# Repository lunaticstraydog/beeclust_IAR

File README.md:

# Implementation of an adated beeclust algorithm for mona robot
## Implementation details
3 versions :
version 1 is less sensitive (robots will not detect each others at great distances) and will work with a robot acting as the source (with light_emitter)
Version 2 is more sensitive and aggregates quicker generally.
It also is confirmed to work with a standard lamp acting as an IR source.
A few things to note :
- It is technically possible for a robot to wrongfully detect another robot as the source in the second algorithm, thought it did not happen in our testing
- The robot is supposed to wait longer (led are red in that case) the more robots it detected. (in the second algorithm).
	However, right now it only takes into account the robots it first detected, which is suboptimal and makes that feature work fairly badly (most often it will just consider one robot around it regardless)
- Blue state means the robot thinks it saw a source (in the second algo).
	In the subsequent 5 seconds ~ it will monitor its sensors to check whether it really was a source.
	It happens that it will mistake a robot for a source, will turn blue but will later change its mind. This is normal behavior.

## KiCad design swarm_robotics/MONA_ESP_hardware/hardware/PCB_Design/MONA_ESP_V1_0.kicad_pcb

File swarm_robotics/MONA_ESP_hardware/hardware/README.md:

# MONA ESP Hardware

## Schematic
The schematic for the board is given in a PDF file. The value of passive components is shown and the component code of the IC. 

## PCB design file
The PCB board file is given in [KiCad](www.kicad.org) format. It is neccesarry to use KiCad to open the board file.

## MONA ESP board design

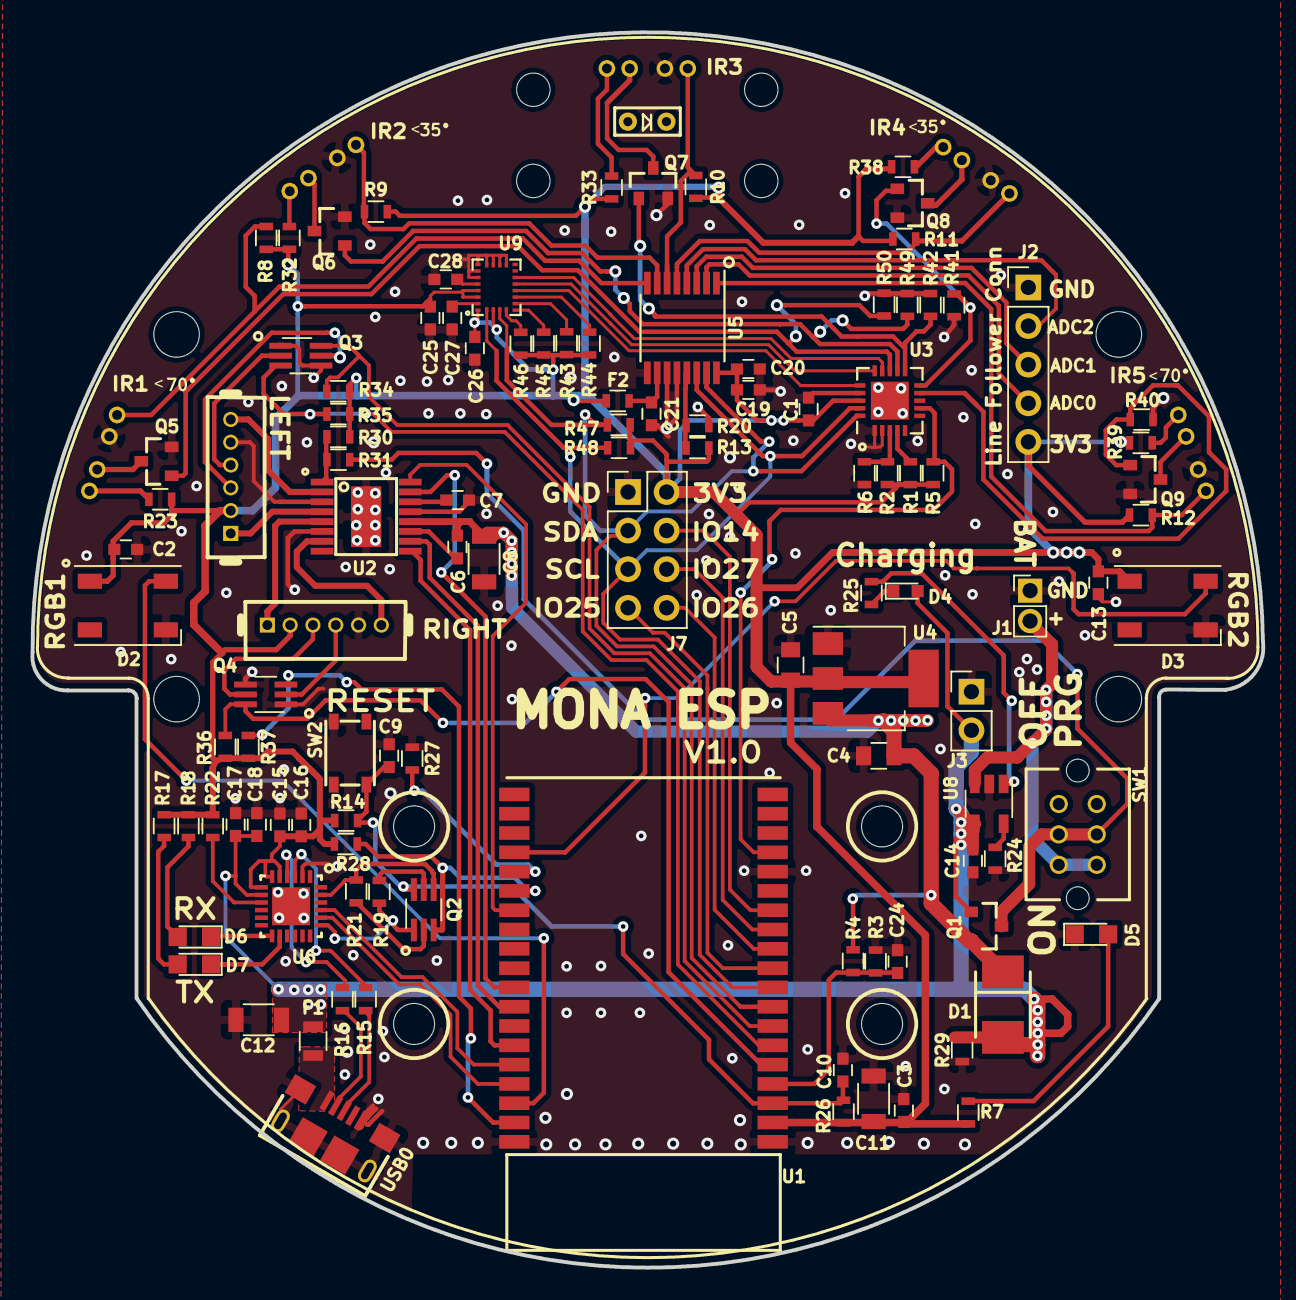
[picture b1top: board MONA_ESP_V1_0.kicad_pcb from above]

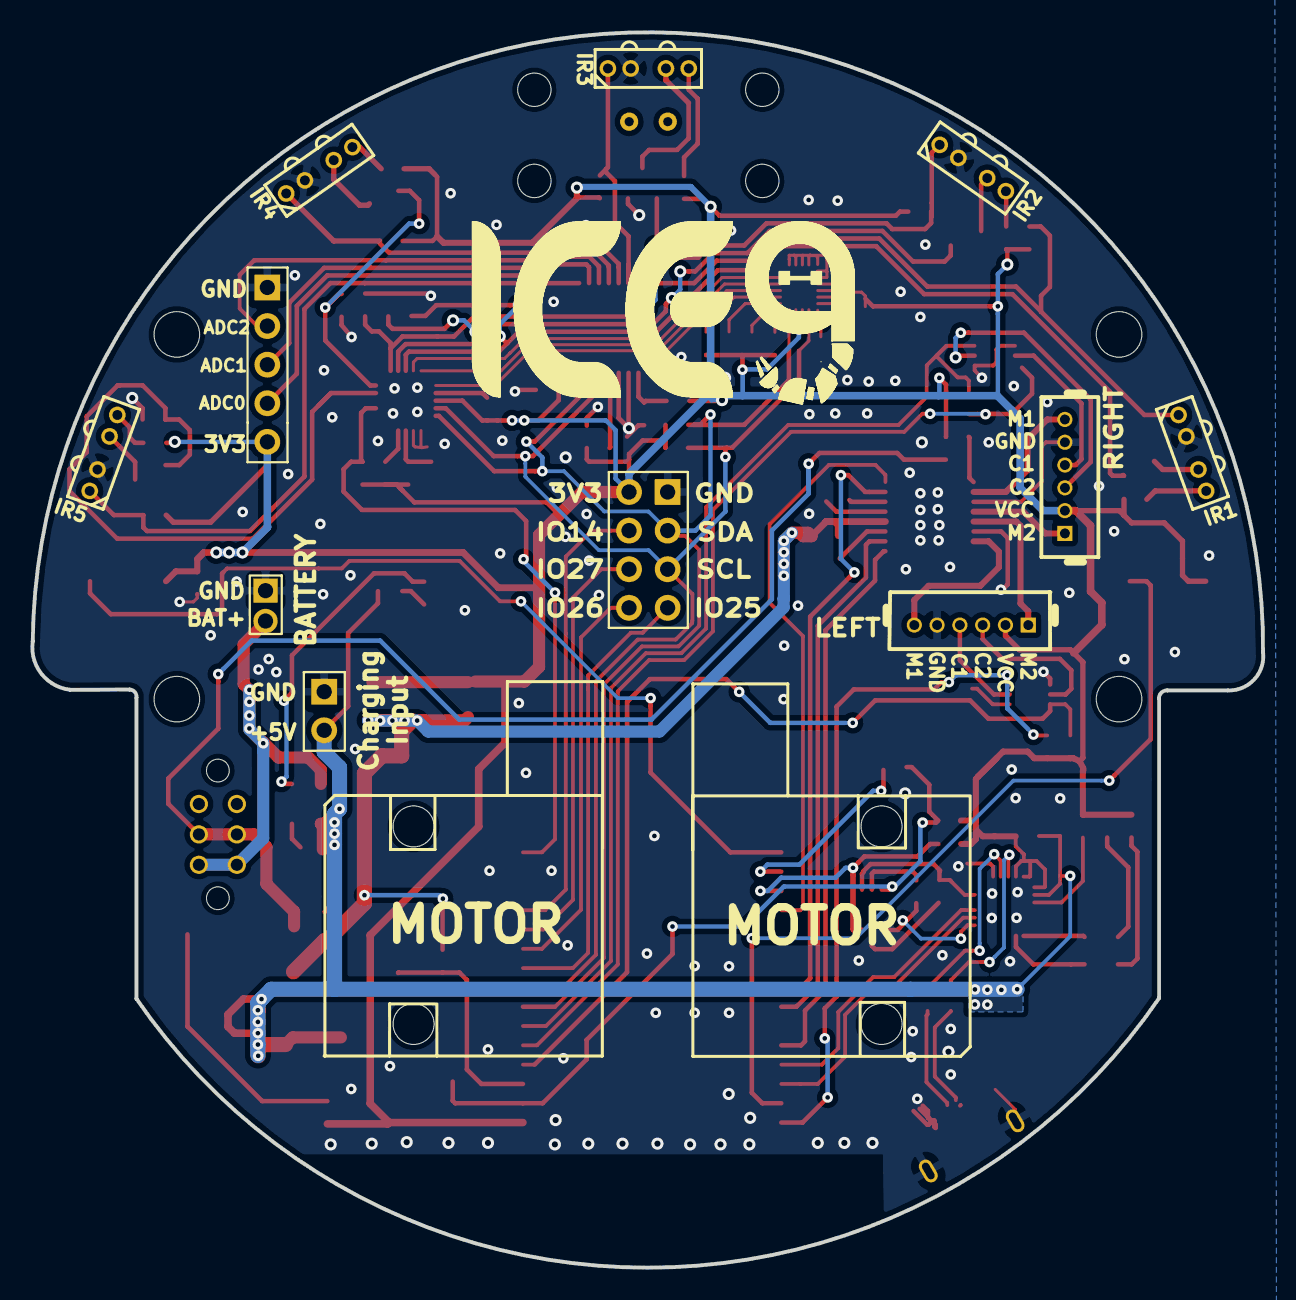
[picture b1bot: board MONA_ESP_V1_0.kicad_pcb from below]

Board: 2 copper layers, 81.0 x 81.3 mm, 129 parts (5 on the bottom side), 95 nets.

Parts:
C1, C2, C3, C13: 1uF , 10V; C_0603
C4, C5: 10uF , 10V; C_0805
C6: 10nF , 10V; C_0603
C7: 2.2uF , 10V; C_0603
C8, C12: 10uF , 10V; C_1206
C9: 100pF , 50V; C_0603
C10, C14, C15, C24, C25, C26, C27: 0.1uF , 10V; C_0603
C11: 100uF , 6.3V; C_1206
C16: 4.7uF , 6V; C_0603
C17: 1uF,10V; C_0603
C18: 0.1uF , 6V; C_0603
C19: 1uf; C_0603
C20, C21: 100nF; C_0603
C28: 0.01uF , 10V; C_0603
D1: Schottky_403A; SMB_403A
D2, D3: WS2812B; LED_WS2812B-PLCC4
D4: LED; LED_0603
D5, D6, D7, D8: LED; LED_0805
F1: Ferrite_Bead; L_0805
F2: Ferrite_Bead; L_0603
IR1, IR2, IR3, IR4, IR5: TCRT1000
J1: Conn_01x02 1.8mm pitch; BAT_conn_1x02_Pitch1.8mm
J2: Conn_01x05; Pin_Header_Straight_1x05_Pitch2.54mm
J3: Conn_01x02; Pin_Header_Straight_1x02_Pitch2.54mm
J7: Conn_02x04_Odd_Even; Pin_Header_Straight_2x04_Pitch2.54mm
M1, M2, M3, M5: Mounting_Hole; MountingHole_3mm
M6, M7, M8, M9: Mounting_Hole; MountingHole_2.7mm_M2.5
M10, M11, M12, M13: Mounting_Hole; MountingHole_2.2mm_M2
ML1: Motor connector 01x06 1.5mm; Pin_Header_Straight_1x06_Pitch1.27mm
MR1: Motor connector 01x06 1.5mm; Pin_Header_Straight_1x06_Pitch1.27mm
Q1: CPH3348-TL-W; SOT-23
Q2, Q3, Q4: MBT3904DW1; SOT-363_SC-70-6_Handsoldering
Q5, Q6, Q7, Q8, Q9: FDV303N; SOT-23
R1, R5, R43, R44, R45, R46: 10k; R_0603
R2, R13, R30: NC; R_0603
R3: 4.7K; R_0603
R4, R8, R9, R10, R11, R12: 18K; R_0603
R6, R20: 0; R_0603
R7, R14, R22, R26, R27, R28: 1K; R_0603
R15, R16: 27R; R_0603
R17, R18: 680R; R_0603
R19, R21: 10K; R_0603
R23, R32, R33, R38, R39: 47; R_0603
R24: 3.3K; R_0603
R25: 330R; R_0603
R29: 100K; R_0603
R31: 0Ohm; R_0603
R34, R35, R36, R37, R47, R48: 1k; R_0603
R40, R41, R42, R49, R50: 100k; R_0603
SW1: OS202011MS2QS1
SW2: PTS810SJK250SMTR; PTS810
U1: ESP32-WROVER-B; ESP32_WROVER_B
U2: DRV8833; HTSSOP-16
U3: MCP23008_QFN; QFN-20-1EP_4x4mm_Pitch0.5mm
U4: NCP1117-3.3_SOT223; SOT-223-3_TabPin2
U5: ADS7830; TSSOP-16_4.4x5mm_Pitch0.65mm
U6: CP2102N; QFN24
U8: LTC4054ES5-4.2; TSOT-23-5
U9: LSM9DS1TR; LGA24-3.5X3.0MM
USB0: AMPHENOL-10118193-0001LF

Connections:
+3V3: C1.2, C2.1, C3.1, C5.2, C11.1, C13.1, C15.2, C16.1, C19.1, C20.1, C25.2, C26.2, D2.1, D3.1, F2.1, J2.5, J7.2, ML1.2, MR1.2, R1.1, R2.1, R5.1, R7.1, R8.2, R9.2, R10.2, R11.2, R12.2, R13.1, R14.2, R17.2, R18.2, R22.2, R23.1, R26.1, R28.1, R30.2, R32.1, R33.1, R34.1, R35.1, R36.1, R37.1, R38.1, R39.1, R43.2, R44.1, R45.2, R46.2, R47.2, R48.2, U1.2, U3.18, U4.2, U5.16, U6.5, U6.6, U6.7, U9.1, U9.3, U9.22, U9.23
/ADC_0: J2.4, U5.2
/ADC_1: J2.3, U5.3
/ADC_2: J2.2, U5.4
/BATT_post_Switch: Q1.3, R31.2, SW1.2, SW1.5
/C1_L: ML1.4, Q3.2
/C1_R: MR1.4, Q4.2
/C2_L: ML1.3, Q3.5
/C2_R: MR1.3, Q4.5
/CHRG: R25.2, U8.1
/CP_DTR: Q2.4, R21.2, U6.23
/CP_RTS: Q2.1, R19.1, U6.19
/CP_RX: U1.35, U6.20
/CP_TX: U1.34, U6.21
/D+: R15.1, USB0.3
/D-: R16.1, USB0.2
/ESP_ADC0: C24.2, R3.2, R4.1, U1.4
/ESP_EN: C9.2, C10.1, Q2.6, R14.1, R26.2, SW2.2, U1.3
/ESP_GPIO4: U1.26, U2.16
/ESP_GPIO14: J7.4, U1.13
/ESP_GPIO15: D3.4, U1.23
/ESP_GPIO18: U1.30, U2.15
/ESP_GPIO19: U1.31, U2.10
/ESP_GPIO21: U1.33, U2.9
/ESP_GPIO22: D2.4, U1.36
/ESP_GPIO23: Q4.3, R37.2, U1.37
/ESP_GPIO25: J7.7, U1.10
/ESP_GPIO26: J7.8, U1.11
/ESP_GPIO27: J7.6, U1.12
/ESP_GPIO34: Q3.3, R35.2, U1.6
/ESP_GPIO35: Q3.6, R34.2, U1.7
/ESP_GPIO39: Q4.6, R36.2, U1.5
/ESP_IO0: Q2.3, R28.2, U1.25
/ESP_IO2: R27.1, U1.24
/ESP_SCL: J7.5, R48.1, U1.9, U3.19, U5.14, U9.2
/ESP_SDA: J7.3, R47.1, U1.8, U3.20, U5.15, U9.4
/IMU_DRDY: U3.16, U9.9
/IMU_INT_AG: U3.14, U9.11
/IMU_INT_M: U3.15, U9.10
/IR1_ADC: IR1.4, R8.1, U5.8
/IR1_E: Q5.1, R50.1, U3.13
/IR2_ADC: IR2.4, R9.1, U5.7
/IR2_E: Q6.1, R49.1, U3.12
/IR3_ADC: IR3.4, R10.1, U5.6
/IR3_E: Q7.1, R42.1, U3.11
/IR4_ADC: IR4.4, R11.1, U5.5
/IR4_E: Q8.1, R41.1, U3.10
/IR5_ADC: IR5.4, R12.1, U5.1
/IR5_E: Q9.1, R40.1, U3.9
/M1_L: ML1.6, U2.2
/M1_R: MR1.6, U2.7
/M2_L: ML1.1, U2.4
/M2_R: MR1.1, U2.5
/MPC_INT: R5.2, U1.16, U3.7
/RAW_BATT: J1.2, SW1.1, SW1.4, U8.3
/VBUS: F1.1, USB0.1
/VBUS_FIL: C12.2, C14.2, C17.2, C18.2, D1.A, D4.2, F1.2, J3.2, Q1.1, R29.2, U6.8, U8.4
GND: C1.1, C2.2, C3.2, C4.1, C5.1, C7.1, C8.2, C9.1, C10.2, C11.2, C12.1, C13.2, C14.1, C15.1, C16.2, C17.1, C18.1, C19.2, C20.2, C21.1, C24.1, C25.1, C26.1, C27.1, C28.1, D2.3, D3.3, D5.1, IR1.3, IR2.3, IR3.3, IR4.3, IR5.3, J1.1, J2.1, J3.1, J7.1, ML1.5, MR1.5, Q3.1, Q3.4, Q4.1, Q4.4, Q5.2, Q6.2, Q7.2, Q8.2, Q9.2, R3.1, R6.2, R20.2, R24.1, R27.2, R29.1, R40.2, R41.2, R42.2, R49.2, R50.2, SW2.3, U1.1, U1.15, U1.38, U2.3, U2.6, U2.13, U3.1, U3.2, U3.17, U3.21, U4.1, U5.9, U5.11, U5.12, U6.2, U6.25, U8.2, U9.14, U9.15, U9.16, U9.17, U9.18, U9.19, U9.20, USB0.5, USB0.SH1, USB0.SH2, USB0.SH3, USB0.SH4, USB0.SH5, USB0.SH6
unnamed: C6.1, U2.11
unnamed: C7.2, U2.14
unnamed: C21.2, F2.2, U5.10
unnamed: C27.2, U9.24
unnamed: C28.2, U9.21
unnamed: D4.1, R25.1
unnamed: D5.2, R7.2
unnamed: D6.1, U6.13
unnamed: D6.2, R18.1
unnamed: D7.1, U6.14
unnamed: D7.2, R17.1
unnamed: IR1.1, R23.2
unnamed: IR1.2, Q5.3
unnamed: IR2.1, R32.2
unnamed: IR2.2, Q6.3
unnamed: IR3.1, R33.2
unnamed: IR3.2, Q7.3
unnamed: IR4.1, R38.2
unnamed: IR4.2, Q8.3
unnamed: IR5.1, R39.2
unnamed: IR5.2, Q9.3
unnamed: Q2.2, R21.1
unnamed: Q2.5, R19.2
unnamed: R1.2, U3.4
unnamed: R2.2, R6.1, U3.3
unnamed: R13.2, R20.1, U5.13
unnamed: R15.2, U6.3
unnamed: R16.2, U6.4
unnamed: R22.1, U6.9
unnamed: R24.2, U8.5
unnamed: R30.1, R31.1, U2.1
unnamed: R43.1, U9.7
unnamed: R44.2, U9.8
unnamed: R45.1, U9.6
unnamed: R46.1, U9.5
unnamed: U3.5, U3.6, U3.8
VCC: C4.2, C6.2, C8.1, D1.K, Q1.2, R4.2, U2.12, U4.3

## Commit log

2022-01-03 added everything
2022-01-12 Updated 2.0
2022-01-13 Temp files
2022-01-14 Changement de la structure des fichiers + Readme
2022-01-27 Rename beeclust2.ino to beeclust.ino
